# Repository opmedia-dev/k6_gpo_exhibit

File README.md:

# K6 GPO Exhibit

ESP32-based interface that lets an **unmodified** GPO 232 or 332 rotary-dial
telephone work as an interactive exhibit in a K6 phone box.

## Features

- **Random ringing** — the phone rings at configurable random intervals
  (default 5-30 min); answering plays a randomly selected history track
- **Dial-a-number** — dial up to 11 digits; if a matching MP3 exists on the
  SD card it plays, otherwise a "number not recognised" message plays
- **External control box** — three buttons (RING / CANCEL / RESET) on the
  operator's equipment box, connected via an extended lead
- **Full GPO phone interface** — hook detection, rotary pulse decoding, bell
  ringing (25 Hz UK cadence), all through the original 3-core cord
- **SD card audio** — all audio (history tracks, number tracks, dial tone,
  busy tone) loaded from a micro-SD card as MP3 files
- **I2S audio output** — MAX98357A DAC for quality playback through the
  phone's earpiece via a coupling transformer
- **Optional A+B coin box** — auto-detected daughter board supports classic
  GPO pre-payment coin mechanisms (Button A/B, coin weight switch)
- **Auto/Manual mode** — 4th button toggles auto-ring on/off with panel lamp
  indicator (GPIO 13, 3–6 V)
- **Wi-Fi file manager** — ESP32 creates a `K6-Exhibit` Wi-Fi hotspot;
  connect from any phone/laptop browser to upload, delete, and manage
  SD card files without removing the card
- **OTA firmware update** — upload a compiled `.bin` through the web
  interface to update firmware wirelessly
- **System & call logging** — separate logs for system events and call
  history, viewable and clearable via the web interface

No modifications are made to the telephone.

## Supported Phones

| Phone | Bell | Notes |
|-------|------|-------|
| GPO 232 | External (Bellset No. 26) | Blue wire drives external bell, or leave unconnected |
| GPO 332 | Internal (2 µF cap + bell coils) | Full bell ringing via blue wire |
| GPO 332L | Internal | "Listener" variant, same 3-wire connection |

Any GPO phone with a 3-wire connection (Line A, Line B, Bell) should work.
See the hardware docs for notes on other models (706, 746, etc.).

## System Architecture

```
┌─────────────┐   3-core cord    ┌─────────────────────────────┐
│  GPO Phone  │ ◄──────────────► │   ESP32 Interface Board     │
│  (unmod.)   │  extended lead   │   (in separate enclosure)   │
└─────────────┘                  │                             │
                                 │  ESP32 DevKit               │
                                 │  + SD card module           │
                                 │  + MAX98357A I2S DAC        │
                                 │  + L293D H-bridge (ringer)  │
                                 │  + 12V adapter → buck (5V)  │
                                 │  + 48V adapter (bell supply)│
                                 │  + Optocoupler (line sense) │
                                 │  + 4 control buttons        │
                                 └─────────────────────────────┘
```

## Hardware

See [`docs/hardware/`](docs/hardware/) for:
- [**Schematic**](docs/hardware/schematic.md) — full circuit with ASCII diagrams
- [**Bill of Materials**](docs/hardware/bom.md) — ~£29 in components
- [**Wiring Guide**](docs/hardware/wiring-guide.md) — step-by-step build + test

### PCB

A KiCad carrier board layout is in [`pcb/`](pcb/) — 100 × 100 mm, 2-layer,
all through-hole.  All modules (ESP32 DevKit, MAX98357A, SD card, LM2596
buck converter) plug in via pin headers; the bell runs from a dedicated
48 V adapter.  The **as-built, bench-proven manufacturing master is
[`pcb/k6_carrier_rev2-8.kicad_pcb`](pcb/k6_carrier_rev2-8.kicad_pcb)** —
use it for reorders.  See [`pcb/README.md`](pcb/README.md) for fabrication
instructions.

## SD Card Setup

Format a micro-SD card as FAT32 and create this directory structure:

```
/system/
    dialtone.mp3           Continuous dial tone (loops while off-hook)
    busy.mp3               Busy / error tone (loops)
    not_recognised.mp3     "The number you have dialled…"
/history/
    001.mp3                History track 1 (picked at random on ring answer)
    002.mp3                History track 2
    …
/numbers/
    999.mp3                Plays when user dials 999
    100.mp3                Plays when user dials 100
    08001111.mp3           Plays when user dials 08001111
    …
```

- History tracks play when the phone rings and is answered
- Number tracks are matched by filename: dialling `999` looks for `/numbers/999.mp3`
- If no match is found, `/system/not_recognised.mp3` plays

## Wi-Fi File Manager

The ESP32 creates a Wi-Fi access point on boot:

| Setting | Value |
|---------|-------|
| SSID | `K6-Exhibit` |
| Password | `phonebox` |
| URL | `http://192.168.4.1/` |

Connect with any phone or laptop, open a browser, and you can:
- **Controls** — volume slider, auto-ring timing, mode toggle, Ring Now button
- **Visitor stats** — call counters, most-dialled numbers, total uptime
- **Browse** the SD card directory structure
- **Upload** new MP3 files (validated as valid MP3 before saving)
- **Delete** existing files
- **Create** new folders
- **View logs** — system events and call history (separate tabs)
- **Clear logs** — wipe system or call log
- **Flash firmware** — upload a `.bin` file for OTA update
- **System status** — free heap, SD card space (used/total), current state

### Logs

| Log | Path | Contents |
|-----|------|----------|
| System | `/logs/system.log` | Boot, Wi-Fi, SD card, mode changes, OTA, errors |
| Calls | `/logs/calls.log` | Incoming/outgoing calls with timestamps, numbers, outcomes |

Logs auto-rotate at 64 KB to avoid filling the SD card.

## Firmware

Built with [PlatformIO](https://platformio.org/) (Arduino framework for ESP32).

### Build & Flash

```bash
cd firmware
pio run                    # compile
pio run -t upload          # flash to ESP32
pio device monitor         # serial console (115200 baud)
```

### Serial Commands

| Command | Action |
|---------|--------|
| `R` | Ring the bell |
| `H` | Hang up / stop everything |
| `C` | Cancel ring / stop playback |
| `S` | Print current state + diagnostics |
| `A` | Toggle auto-ring on/off |
| `V0`-`V9` | Set volume (0 = min, 9 = max) |

### Control Panel Buttons

| Button | Function |
|--------|----------|
| RING (GPIO 32) | Manually trigger the phone bell |
| CANCEL (GPIO 33) | Cancel ringing / stop current playback |
| RESET (GPIO 27) | Full system restart |
| MODE (GPIO 14) | Toggle auto/manual ring mode |

All buttons are active-low (connect to GND when pressed); the ESP32's
internal pull-ups are enabled.

### Auto-Mode Indicator Lamp

GPIO 13 drives a 3–6 V panel lamp (active-high) that illuminates when
auto-ring mode is active.  In **auto mode** the phone rings at random
intervals (5–30 min) and the lamp is ON.  In **manual mode** the phone
only rings when the RING button is pressed and the lamp is OFF.
Calling (lifting the handset, dialling) works in both modes.

### Firmware Architecture

```
main.cpp                    Arduino setup/loop, serial commands
  └─ PhoneController        Top-level state machine
       ├─ PhoneLine         Hook detection via optocoupler + ADC
       ├─ RotaryDecoder     Dial pulse counting → digit
       ├─ BellDriver        25 Hz H-bridge with UK ring cadence
       ├─ AudioPlayer       SD card MP3 playback via I2S
       ├─ ControlPanel      3-button debounced input
       └─ CoinBox           Optional A+B coin box (auto-detected)
```

State machine:

```
             auto-ring timer
                  or
IDLE ──── BTN_RING/serial 'R' ──── RINGING ──── (answer) ──── PLAYING_HISTORY
  │                                                                 │
  │                                                            (on-hook)
  │                                                                 │
  └── (lift handset) ── DIAL_TONE ── DIALING ─┬── PLAYING_NUMBER ──┘
                                               │         │
                                               │    (playback ends) ── BUSY ── (on-hook) ── IDLE
                                               │
                              [A+B, recognised] ├── AWAIT_COINS ── (coins in) ── AWAIT_BTN_A
                                               │                   "press A" prompt
                              [A+B, coins in]  ├── AWAIT_BTN_A ── (Btn A) ── PLAYING_NUMBER
                                               │                  (Btn B) ── IDLE (refund)
                                               │
                          [A+B, not recognised] └── AWAIT_BTN_B ── (Btn B) ── IDLE (refund)
                                                    "not recognised" then "press B" prompt

Without A+B: DIALING → PLAYING_NUMBER or PLAYING_NOT_REC directly.
Incoming calls (RINGING → answer) never require A+B interaction.
```

### Callbacks

```cpp
phone.onDigit(       { /* each digit as dialled */ });
phone.onNumber(  { /* complete number string */ });
phone.onHook(      { /* hook state change */     });
phone.onState(    { /* state transition */      });
```

## Pin Assignments

| GPIO | Function |
|------|----------|
| 34 | Line sense (hook / dial pulse) — ADC input |
| 26 | I2S BCLK (to MAX98357A) |
| 25 | I2S LRCLK (to MAX98357A) |
| 22 | I2S DOUT (to MAX98357A) |
| 5 | SD card CS (SPI) |
| 23 | SD card MOSI |
| 19 | SD card MISO |
| 18 | SD card SCK |
| 4 | Ring enable (H-bridge EN) |
| 16 | Ring phase A (H-bridge IN1) |
| 17 | Ring phase B (H-bridge IN2) |
| 32 | Button: RING (active-low) |
| 33 | Button: CANCEL (active-low) |
| 27 | Button: RESET (active-low) |
| 14 | Button: MODE (active-low) |
| 13 | Auto-mode lamp (active-high, 3–6 V) |
| 2 | Status LED |
| 36 | Coin box: coin sense (optional, input-only) |
| 39 | Coin box: Button A (optional, input-only) |
| 35 | Coin box: Button B (optional, input-only) |

## Technical Reference

See [`docs/gpo-phone-reference.md`](docs/gpo-phone-reference.md) for detailed
GPO 232/332 electrical specifications, rotary dial pulse characteristics, and
bell ringing requirements.

## Future Enhancements

- **Wi-Fi / MQTT** integration for remote exhibit control
- **Multi-phone networking** — connect two GPO phones via ESP-NOW
- **VoIP gateway** — bridge the GPO phone to SIP/VoIP
- **A+B coin box daughter board** — PCB design for coin mechanism interface
- **OLED status display** on the operator's control box

## License

MIT

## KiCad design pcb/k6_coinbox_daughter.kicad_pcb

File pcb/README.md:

# PCB — K6 GPO Exhibit Carrier Board

KiCad 10 project for a 2-layer carrier board (100 × 100 mm).  All modules
plug in via through-hole pin headers — no SMD soldering required.

See **[PINOUT.md](PINOUT.md)** for the complete pinout reference with every
pin, net, and signal described.

## Files

| File | Description |
|------|-------------|
| `k6_gpo_carrier.kicad_pro` | KiCad project file |
| `k6_gpo_carrier.kicad_sch` | Schematic (text-documentation style — shows all nets and pin assignments) |
| `k6_gpo_carrier.kicad_pcb` | PCB layout with component placement, ground-fill zones, and board outline |
| `generate_kicad.py` | Python script that generates all files above (run to regenerate) |
| `PINOUT.md` | Complete pinout reference (full tables for every connector and IC) |
| `k6_carrier_rev2-8.kicad_pcb` | **Hand-routed manufacturing master (Rev 2.1, as-built & bench-proven).** Use this file for reorders. Includes the Rev 2.1 fixes: R7 (R_LIM 2.2 kΩ) and D1 in series in the opto leg, C3 (10 µF/63 V coupling cap) in series with the transformer secondary, and R2 (470 Ω) as the opto-LED shunt. Power/48 V nets widened. Not generated by the scripts — edit here directly. |

> **Reorders:** fabricate from `k6_carrier_rev2-8.kicad_pcb`. The
> `generate_*.py` scripts produce the earlier auto-layout boards and do
> **not** include the hand-routed Rev 2.1 corrections above — regenerating
> will not reproduce this master. Before ordering: continuity-check the
> built board, confirm R7 is populated in series, and confirm D1's banded
> (cathode) end faces the PC817 side.

## Board Specifications

| Parameter | Value |
|-----------|-------|
| Dimensions | 100 × 100 mm |
| Layers | 2 (F.Cu + B.Cu) |
| Copper weight | 1 oz |
| Board thickness | 1.6 mm |
| Mounting holes | 4× M3, 4 mm from edges |
| Min trace width | 0.5 mm (power) / 0.25 mm (signal) |
| Min drill | 0.4 mm (vias), 0.8 mm (IC pads), 1.0 mm (headers) |

## Component Placement

```
┌──────────────────────────────────────────────────────────────────────────────┐
│ (MH)  [12V IN]  [BUCK]   [BOOST]                [MAX98357A] [DAC] (MH)     │
│         J3       J1        J2                      J5        J6             │
│                                                                             │
│                                                    [XFMR T1]               │
│                 ┌─────────────────────┐                                     │
│                 │                     │            [PHONE J4]               │
│                 │    ESP32 DevKit     │             3-pin screw             │
│                 │        U1           │                                     │
│ [BUTTONS]       │  2×15 pin headers   │                                     │
│  J8 RING        └─────────────────────┘       [C1]                         │
│  J9 CANCEL                                                                  │
│  J10 RESET                                    ┌────────┐                   │
│                                               │ L293D  │                   │
│                                               │  U2    │                   │
│                 [R1 470R]  [R2 220R]          └────────┘  [R3 10K]         │
│ [SD CARD]                                     ┌────┐                       │
│  J7                                           │PC817│                      │
│                                               │ U3  │                      │
│ (MH)                                          └────┘            (MH)       │
└──────────────────────────────────────────────────────────────────────────────┘
  (MH) = Mounting hole M3
```

## Connectors

| Ref | Description | Pins |
|-----|-------------|------|
| J1 | LM2596 buck converter (12V → 5V) | 4: IN+, IN-, OUT+, OUT- |
| J2 | XL6009 boost converter (12V → 50V) | 4: IN+, IN-, OUT+, OUT- |
| J3 | 12V DC power input | 2: +12V, GND |
| J4 | Phone cord (3-pin screw terminal) | 3: Line A, Line B, Bell |
| J5 | MAX98357A DAC module | 7: VIN, GND, SD, GAIN, DIN, BCLK, LRC |
| J6 | DAC audio output (to transformer) | 2: L+, L- |
| J7 | SD card module (SPI) | 6: GND, VCC, MOSI, MISO, SCK, CS |
| J8 | RING button (to control panel) | 2: signal, GND |
| J9 | CANCEL button (to control panel) | 2: signal, GND |
| J10 | RESET button (to control panel) | 2: signal, GND |

## ICs

| Ref | Part | Package |
|-----|------|---------|
| U1 | ESP32 DevKit V1 | 2×15 pin header socket (25.4 mm row spacing) |
| U2 | L293D H-bridge | DIP-16 (use IC socket) |
| U3 | PC817 optocoupler | DIP-4 (use IC socket) |

## Passive Components

| Ref | Value | Purpose |
|-----|-------|---------|
| R1 | 470 Ω 1W | Line current limit |
| R2 | 220 Ω ¼W | Optocoupler LED current limit |
| R3 | 10 kΩ ¼W | Optocoupler output pull-down |
| C1 | 100 nF | L293D decoupling capacitor |
| T1 | 600 Ω : 600 Ω transformer | Audio coupling to phone line |

## Fabrication

### Ordering from JLCPCB / PCBWay

1. Open the project in KiCad 10+
2. **File → Plot** → select Gerber format, output to `gerbers/`
3. Check layers: F.Cu, B.Cu, F.SilkS, B.SilkS, F.Mask, B.Mask, Edge.Cuts
4. **Generate Drill Files** → Excellon format
5. Zip the `gerbers/` folder and upload to your fabricator

Typical 5-board order from JLCPCB: ~$2 + shipping.

### Assembly Notes

1. Solder IC sockets first (U2 DIP-16, U3 DIP-4)
2. Solder resistors and capacitor
3. Solder pin headers for all module connectors
4. Solder screw terminals (J3 power, J4 phone)
5. Solder transformer T1
6. Insert ICs into sockets (mind pin 1 orientation)
7. Plug in modules: ESP32, MAX98357A, SD card, buck converter, boost converter

## Regenerating Files

If you modify the board layout, edit `generate_kicad.py` and run:

```bash
cd pcb
python3 generate_kicad.py
```

This regenerates all three KiCad files from scratch.

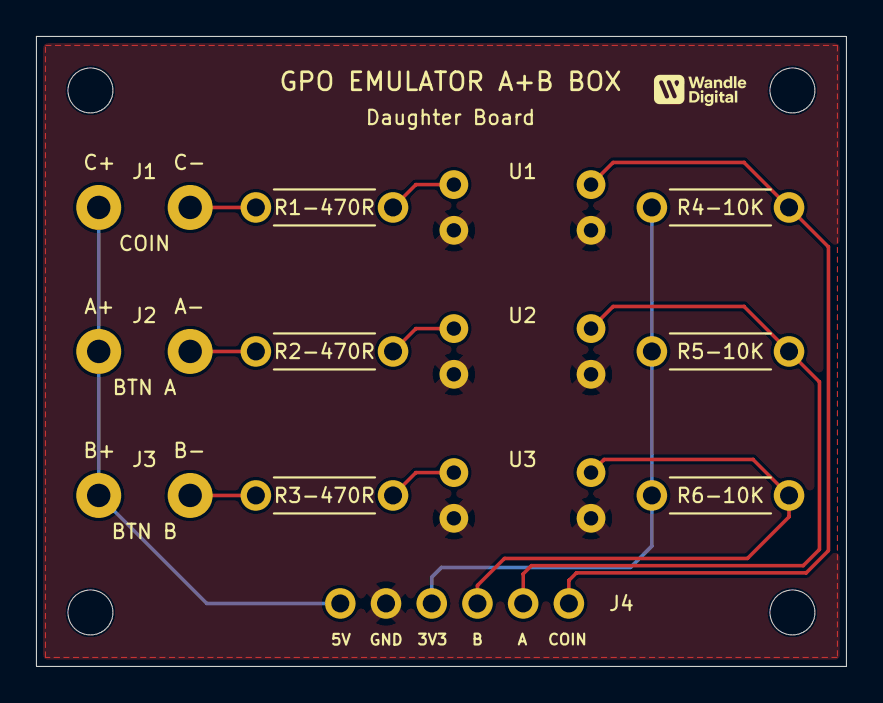
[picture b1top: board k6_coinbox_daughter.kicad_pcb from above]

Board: 2 copper layers, 45.0 x 35.0 mm, 17 parts (0 on the bottom side), 12 nets.

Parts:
J1: COIN; J1
J2: BTN_A; J2
J3: BTN_B; J3
J4: TO_ESP32; J4
MH1: MH; MH1
MH2: MH; MH2
MH3: MH; MH3
MH4: MH; MH4
R1-470R: 470R; R1
R2-470R: 470R; R2
R3-470R: 470R; R3
R4-10K: 10K; R4
R5-10K: 10K; R5
R6-10K: 10K; R6
U1: PC817; U1
U2: PC817; U2
U3: PC817; U3

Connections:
BTNA_IN_B: J2.2, R2-470R.1
BTNB_IN_B: J3.2, R3-470R.1
BTN_A: J4.2, R5-10K.2, U2.4
BTN_B: J4.3, R6-10K.2, U3.4
COIN_IN_B: J1.2, R1-470R.1
COIN_SENSE: J4.1, R4-10K.2, U1.4
GND: J4.5, U1.2, U1.3, U2.2, U2.3, U3.2, U3.3
OPTO1_CA: R1-470R.2, U1.1
OPTO2_CA: R2-470R.2, U2.1
OPTO3_CA: R3-470R.2, U3.1
VCC_3V3: J4.4, R4-10K.1, R5-10K.1, R6-10K.1
VCC_5V: J1.1, J2.1, J3.1, J4.6

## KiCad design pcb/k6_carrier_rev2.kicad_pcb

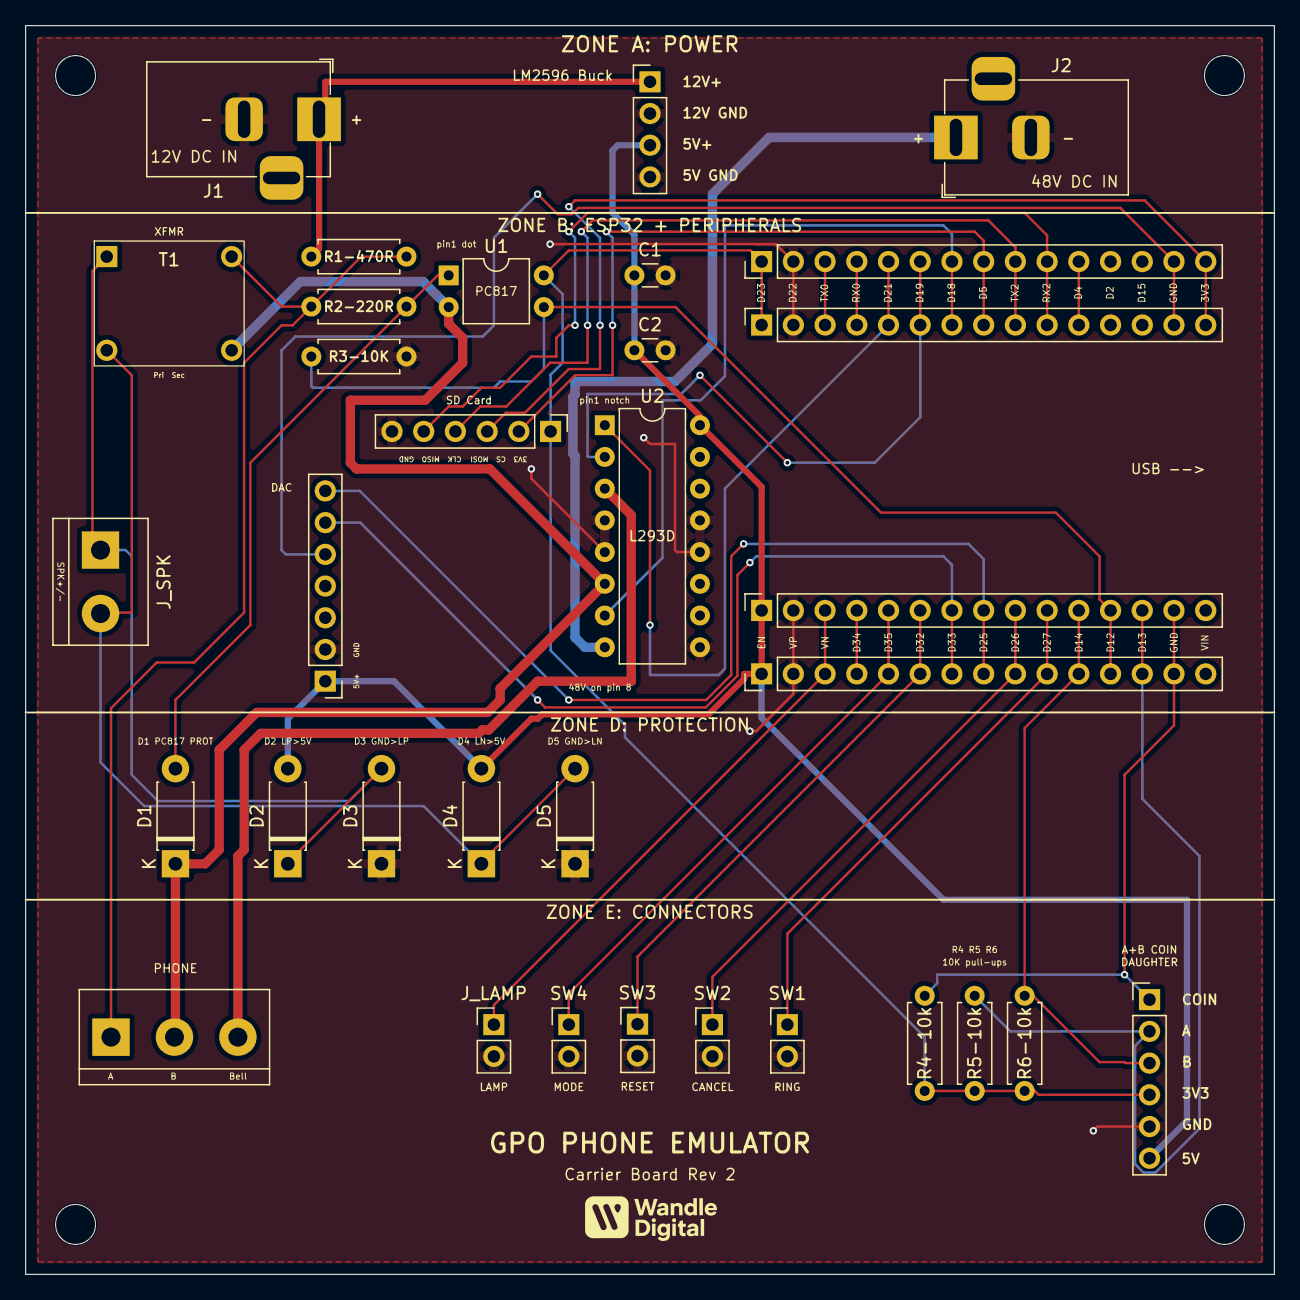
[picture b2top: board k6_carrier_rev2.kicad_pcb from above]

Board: 2 copper layers, 100.0 x 100.0 mm, 37 parts (0 on the bottom side), 34 nets.

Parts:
C1, C2: 100nF; C_Disc_D3.0mm_W1.6mm_P2.50mm
D1, D2, D3, D4, D5: 1N4007; D_DO-41_SOD81_P7.62mm_Horizontal
H1, H2, H3, H4: M3; MountingHole_3.2mm_M3
J1: 12V_DC; BarrelJack_Horizontal
J2: 48V_DC; BarrelJack_Horizontal
J_COIN: A+B; PinHeader_1x06_P2.54mm_Vertical
J_DEV_L: DEV_Left; PinHeader_1x15_P2.54mm_Vertical
J_DEV_R: DEV_Right; PinHeader_1x15_P2.54mm_Vertical
J_ESP_L: ESP32_Left; PinSocket_1x15_P2.54mm_Vertical
J_ESP_R: ESP32_Right; PinSocket_1x15_P2.54mm_Vertical
J_LAMP: Lamp; PinHeader_1x02_P2.54mm_Vertical
J_PHONE: Phone; TerminalBlock_bornier-3_P5.08mm
J_SPK: Speaker; TerminalBlock_bornier-2_P5.08mm
R1-470R: R2-470R; R_Axial_DIN0207_L6.3mm_D2.5mm_P7.62mm_Horizontal
R2-220R: R3-220R; R_Axial_DIN0207_L6.3mm_D2.5mm_P7.62mm_Horizontal
R3-10K, R4-10k, R5-10k, R6-10k: 10K; R_Axial_DIN0207_L6.3mm_D2.5mm_P7.62mm_Horizontal
SW1: RING; PinHeader_1x02_P2.54mm_Vertical
SW2: CANCEL; PinHeader_1x02_P2.54mm_Vertical
SW3: RESET; PinHeader_1x02_P2.54mm_Vertical
SW4: MODE; PinHeader_1x02_P2.54mm_Vertical
T1: 600R_XFMR; PinHeader_2x02_P2.54mm_Vertical
U1: PC817; DIP-4_W7.62mm
U2: L293D; DIP-16_W7.62mm
U_BUCK: LM2596; PinHeader_1x04_P2.54mm_Vertical
U_DAC: MAX98357A; PinHeader_1x07_P2.54mm_Vertical
U_SD: SD_Card; PinHeader_1x06_P2.54mm_Vertical

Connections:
+3V3: J_COIN.4, J_DEV_R.1, J_ESP_R.1, R4-10k.1, R5-10k.1, R6-10k.1, U1.4, U_SD.1
+5V: C1.1, C2.1, D2.2, D4.2, J_COIN.6, J_DEV_L.1, J_ESP_L.1, U2.16, U_BUCK.3, U_DAC.1
+12V: J1.1, R1-470R.1, U_BUCK.1
+48V: J2.1, U2.8
BELL: J_PHONE.3, U2.3
DAC_LN: D4.1, D5.2, J_SPK.2, T1.3
DAC_LP: D2.1, D3.2, J_SPK.1, T1.1
GND: C1.2, C2.2, D3.1, D5.1, J1.2, J2.2, J_COIN.5, J_DEV_L.2, J_DEV_R.2, J_ESP_L.2, J_ESP_R.2, J_LAMP.2, R3-10K.2, SW1.2, SW2.2, SW3.2, SW4.2, U2.4, U2.5, U2.9, U2.12, U2.13, U_BUCK.2, U_BUCK.4, U_DAC.2, U_SD.6
GPIO2: J_DEV_R.4, J_ESP_R.4
GPIO4: J_DEV_R.5, J_ESP_R.5, U2.1
GPIO5: J_DEV_R.8, J_ESP_R.8, U_SD.2
GPIO12: J_DEV_L.4, J_ESP_L.4
GPIO13: J_DEV_L.3, J_ESP_L.3, J_LAMP.1
GPIO14: J_DEV_L.5, J_ESP_L.5, SW4.1
GPIO15: J_DEV_R.3, J_ESP_R.3
GPIO16: J_DEV_R.6, J_ESP_R.6, U2.2
GPIO17: J_DEV_R.7, J_ESP_R.7, U2.7
GPIO18: J_DEV_R.9, J_ESP_R.9, U_SD.4
GPIO19: J_DEV_R.10, J_ESP_R.10, U_SD.5
GPIO21: J_DEV_R.11, J_ESP_R.11
GPIO22: J_DEV_R.14, J_ESP_R.14, U_DAC.5
GPIO23: J_DEV_R.15, J_ESP_R.15, U_SD.3
GPIO25: J_DEV_L.8, J_ESP_L.8, U_DAC.7
GPIO26: J_DEV_L.7, J_ESP_L.7, U_DAC.6
GPIO27: J_DEV_L.6, J_ESP_L.6, SW3.1
GPIO32: J_DEV_L.10, J_ESP_L.10, SW1.1
GPIO33: J_DEV_L.9, J_ESP_L.9, SW2.1
GPIO34: J_DEV_L.12, J_ESP_L.12, R3-10K.1, U1.3
GPIO35: J_COIN.3, J_DEV_L.11, J_ESP_L.11, R6-10k.2
GPIO36: J_COIN.1, J_DEV_L.14, J_ESP_L.14, R4-10k.2
GPIO39: J_COIN.2, J_DEV_L.13, J_ESP_L.13, R5-10k.2
LINE_A: J_PHONE.1, R1-470R.2, R2-220R.1, T1.2
LINE_B: D1.1, J_PHONE.2, T1.4, U1.2, U2.6
OPTO_A: D1.2, R2-220R.2, U1.1

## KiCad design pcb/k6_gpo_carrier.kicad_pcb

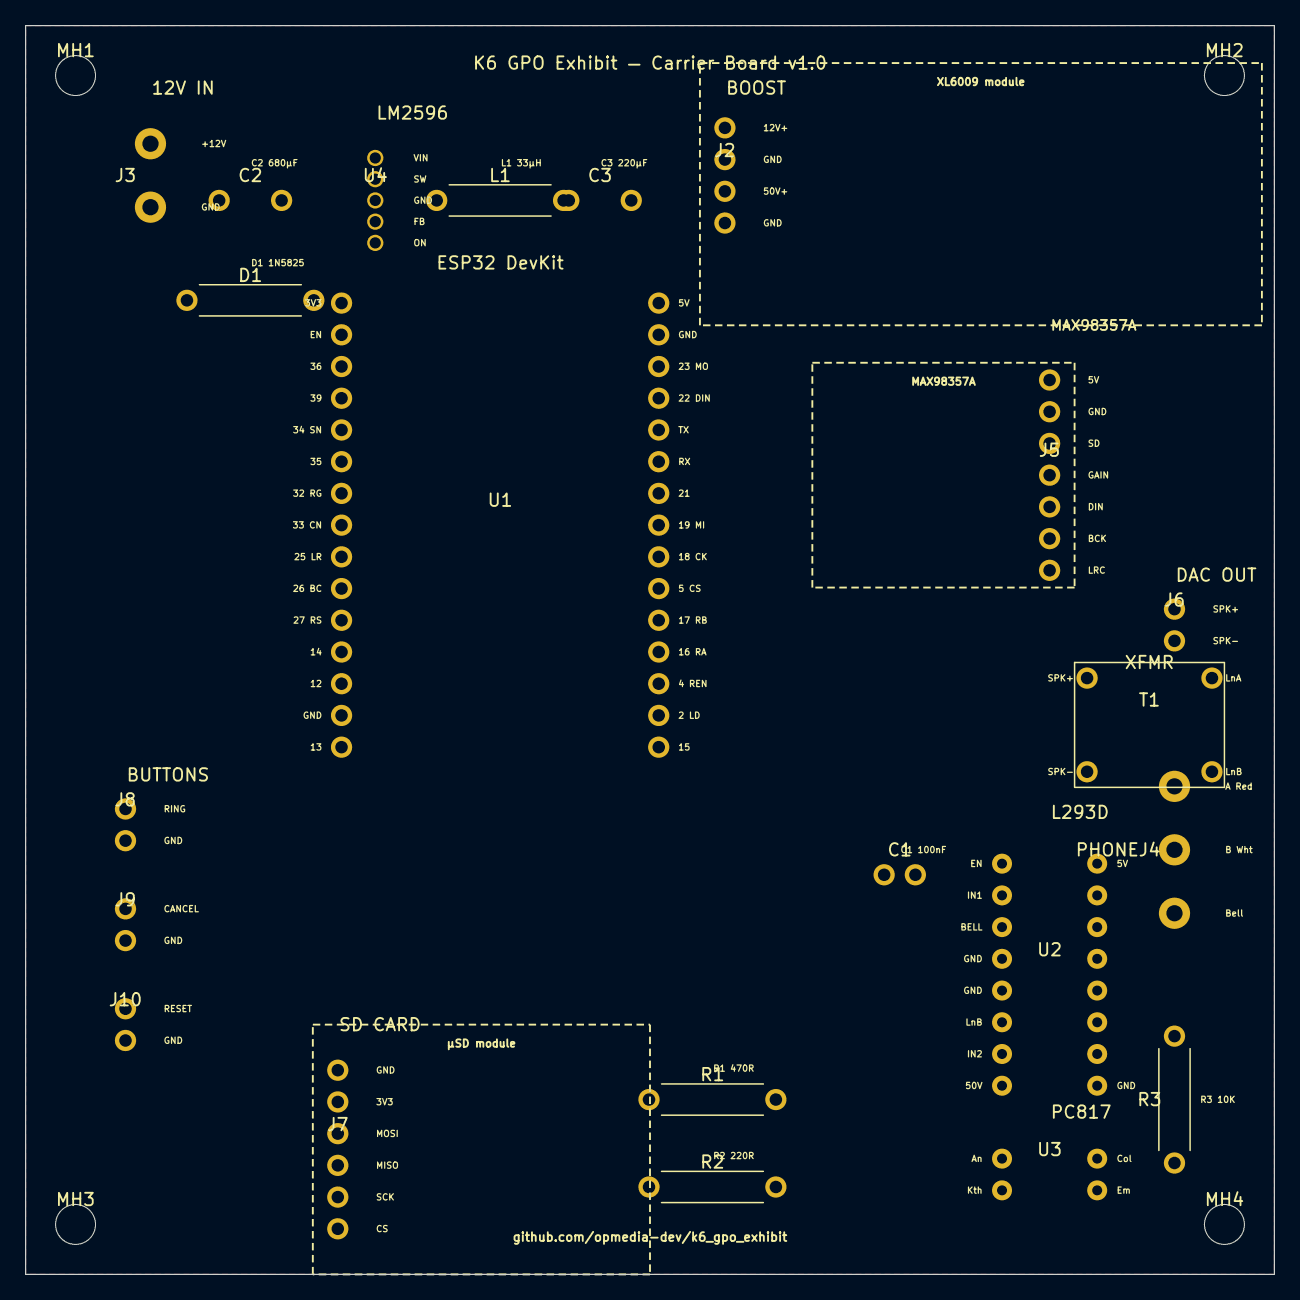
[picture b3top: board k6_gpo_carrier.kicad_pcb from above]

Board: 2 copper layers, 100.0 x 100.0 mm, 26 parts (0 on the bottom side), 27 nets, no tracks yet.

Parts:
C1: 100nF; C1
C2: 680uF; C2
C3: 220uF; C3
D1: 1N5825; D1
J2: XL6009_Boost; J2
J3: 12V_IN; J3
J4: PHONE; J4
J5: MAX98357A; J5
J6: DAC_OUT; J6
J7: SD_Card; J7
J8: BTN_RING; J8
J9: BTN_CANCEL; J9
J10: BTN_RESET; J10
L1: 33uH; L1
MH1: MH; MH1
MH2: MH; MH2
MH3: MH; MH3
MH4: MH; MH4
R1: 470R; R1
R2: 220R; R2
R3: 10K; R3
T1: 600R_XFMR; T1
U1: ESP32_DevKit; U1
U2: L293D; U2
U3: PC817; U3
U4: LM2596-5.0; U4

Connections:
+3V3: J7.2, U1.L1, U3.4
+5V: C1.1, C3.1, J5.1, L1.2, U1.R1, U2.16, U4.4
+12V: C2.1, J2.1, J3.1, R1.1, U4.1
+50V: J2.3, U2.8
AUDIO_P1: J6.1, T1.1
AUDIO_P2: J6.2, T1.2
BELL: J4.3, U2.3
BTN_CANCEL: J9.1, U1.L8
BTN_RESET: J10.1, U1.L11
BTN_RING: J8.1, U1.L7
GND: C1.2, C2.2, C3.2, D1.1, J2.2, J2.4, J3.2, J5.2, J7.1, J8.2, J9.2, J10.2, R3.2, U1.L14, U1.R2, U2.4, U2.5, U2.9, U2.12, U2.13, U4.3, U4.5
I2S_BCLK: J5.6, U1.L10
I2S_DOUT: J5.5, U1.R4
I2S_LRCLK: J5.7, U1.L9
JUNC_A: R1.2, R2.1
LINE_A: J4.1, T1.3
LINE_B: J4.2, T1.4, U2.6, U3.2
OPTO_ANODE: R2.2, U3.1
OPTO_EMIT: R3.1, U3.3
RING_A: U1.R12, U2.2
RING_B: U1.R11, U2.7
RING_EN: U1.R13, U2.1
SD_CS: J7.6, U1.R10
SPI_MISO: J7.4, U1.R8
SPI_MOSI: J7.3, U1.R3
SPI_SCK: J7.5, U1.R9
SW_OUT: D1.2, L1.1, U4.2

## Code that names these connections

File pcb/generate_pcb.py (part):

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
    # ── Nets ──
    net_names = ["", "GND", "+5V", "+3V3", "+12V", "+48V",
        "GPIO4", "GPIO16", "GPIO17", "GPIO26", "GPIO25", "GPIO22",
        "GPIO5", "GPIO23", "GPIO19", "GPIO18",
        "GPIO32", "GPIO33", "GPIO27", "GPIO14",
        "GPIO36", "GPIO39", "GPIO35", "GPIO13", "GPIO34", "GPIO2",
        "LINE_A", "LINE_B", "BELL", "OPTO_A", "DAC_LP", "DAC_LN",
        "GPIO12", "GPIO15", "GPIO21"]
    for i, n in enumerate(net_names):
        board.Add(pcbnew.NETINFO_ITEM(board, n, i))

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    # ── ZONE D: PROTECTION DIODES (y = 57..70mm) ──

    # D1: 1N4007 anti-parallel across PC817 LED (clamps reverse voltage)
    # Anode = LINE_B (PC817 cathode side), Cathode = OPTO_A (PC817 anode side)
    place(board, "Diode_THT", "D_DO-41_SOD81_P7.62mm_Horizontal",
          "D1", "1N4007", OX+10, OY+60)
    text(board, "D1 PC817 PROT", OX+14, OY+57, S, 0.5, 0.08)
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    esp_l_nets = {
        1: "+5V",      # VIN
        2: "GND",
        3: "GPIO13",
        4: "GPIO12",
        5: "GPIO14",
        6: "GPIO27",
        7: "GPIO26",
        8: "GPIO25",
        9: "GPIO33",
        10: "GPIO32",
        11: "GPIO35",
        12: "GPIO34",
        13: "GPIO39",   # VN
        14: "GPIO36",   # VP
        # 15: EN — no net
    }
    for p, n in esp_l_nets.items():
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    esp_r_nets = {
        1: "+3V3",
        2: "GND",
        3: "GPIO15",
        4: "GPIO2",
        5: "GPIO4",
        6: "GPIO16",   # RX2
        7: "GPIO17",   # TX2
        8: "GPIO5",
        9: "GPIO18",
        10: "GPIO19",
        11: "GPIO21",
        # 12: RX0 — no net (serial debug)
        # 13: TX0 — no net (serial debug)
        14: "GPIO22",
        15: "GPIO23",
    }
    for p, n in esp_r_nets.items():
        set_pad_net("J_ESP_R", p, n)
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
    # ── U1 (PC817 optocoupler DIP-4) ──
    # Pin 1=Anode (from R2), Pin 2=Cathode (to Line B),
    # Pin 3=Emitter (GPIO34+R3), Pin 4=Collector (+3.3V)
    set_pad_net("U1", 1, "OPTO_A")
    set_pad_net("U1", 2, "LINE_B")
    set_pad_net("U1", 3, "GPIO34")
    set_pad_net("U1", 4, "+3V3")

    # ── R1 (470Ω) ──  pad 1 = +12V, pad 2 = LINE_A
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    set_pad_net("R2", 1, "LINE_A")
    set_pad_net("R2", 2, "OPTO_A")

    # ── R3 (10kΩ) ──  pad 1 = GPIO34 (opto emitter), pad 2 = GND
    set_pad_net("R3", 1, "GPIO34")
    set_pad_net("R3", 2, "GND")

    # ── U_DAC (MAX98357A 7-pin header) ──
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    set_pad_net("U_DAC", 2, "GND")
    # pin 3 (SD) — leave unconnected (floats high = always on)
    # pin 4 (GAIN) — leave unconnected (default 9dB)
    set_pad_net("U_DAC", 5, "GPIO22")  # DIN
    set_pad_net("U_DAC", 6, "GPIO26")  # BCLK
    set_pad_net("U_DAC", 7, "GPIO25")  # LRC

    # ── J_SPK (speaker screw terminal 2-pin) ──
    # Connects DAC speaker output to transformer primary
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
    # ── U_SD (SD card 6-pin header: 3V3 CS MOSI CLK MISO GND) ──
    set_pad_net("U_SD", 1, "+3V3")     # 3V3
    set_pad_net("U_SD", 2, "GPIO5")    # CS
    set_pad_net("U_SD", 3, "GPIO23")   # MOSI
    set_pad_net("U_SD", 4, "GPIO18")   # CLK
    set_pad_net("U_SD", 5, "GPIO19")   # MISO
    set_pad_net("U_SD", 6, "GND")

    # ── U2 (L293D H-bridge DIP-16) ──
    set_pad_net("U2", 1, "GPIO4")      # EN1,2
    set_pad_net("U2", 2, "GPIO16")     # IN1
    set_pad_net("U2", 3, "BELL")       # OUT1 → Terminal 3 (Bell)
    set_pad_net("U2", 4, "GND")
    set_pad_net("U2", 5, "GND")
    set_pad_net("U2", 6, "LINE_B")     # OUT2 → Terminal 2 (Line B)
    set_pad_net("U2", 7, "GPIO17")     # IN2
    set_pad_net("U2", 8, "+48V")       # VS (motor supply)
    set_pad_net("U2", 9, "GND")
    set_pad_net("U2", 12, "GND")
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    set_pad_net("J_PHONE", 3, "BELL")    # Terminal 3 (Blue / Bell)

    # ── SW1-4 (buttons: pin 1 = GPIO, pin 2 = GND) ──
    set_pad_net("SW1", 1, "GPIO32"); set_pad_net("SW1", 2, "GND")
    set_pad_net("SW2", 1, "GPIO33"); set_pad_net("SW2", 2, "GND")
    set_pad_net("SW3", 1, "GPIO27"); set_pad_net("SW3", 2, "GND")
    set_pad_net("SW4", 1, "GPIO14"); set_pad_net("SW4", 2, "GND")

    # ── J_LAMP (panel lamp 2-pin: GPIO13 + GND) ──
    set_pad_net("J_LAMP", 1, "GPIO13")
    set_pad_net("J_LAMP", 2, "GND")

    # ── R4/R5/R6 (10kΩ pull-ups: pad 1 = +3V3, pad 2 = GPIO) ──
    set_pad_net("R4", 1, "+3V3");  set_pad_net("R4", 2, "GPIO36")
    set_pad_net("R5", 1, "+3V3");  set_pad_net("R5", 2, "GPIO39")
    set_pad_net("R6", 1, "+3V3");  set_pad_net("R6", 2, "GPIO35")

    # ── J_COIN (daughter board 6-pin header) ──
    set_pad_net("J_COIN", 1, "GPIO36")   # COIN_SENSE
    set_pad_net("J_COIN", 2, "GPIO39")   # BTN_A
    set_pad_net("J_COIN", 3, "GPIO35")   # BTN_B
    set_pad_net("J_COIN", 4, "+3V3")     # Power
    set_pad_net("J_COIN", 5, "GND")
    set_pad_net("J_COIN", 6, "+5V")      # Optional 5V
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
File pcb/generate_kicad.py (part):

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    7: "LINE_B",
    8: "BELL",
    9: "LINE_SENSE",      # GPIO 34
    10: "RING_EN",        # GPIO 4
    11: "RING_A",         # GPIO 16
    12: "RING_B",         # GPIO 17
    13: "I2S_BCLK",       # GPIO 26
    14: "I2S_LRCLK",      # GPIO 25
    15: "I2S_DOUT",       # GPIO 22
    16: "SD_CS",          # GPIO 5
    17: "SPI_MOSI",       # GPIO 23
    18: "SPI_MISO",       # GPIO 19
    19: "SPI_SCK",        # GPIO 18
    20: "BTN_RING",       # GPIO 32
    21: "BTN_CANCEL",     # GPIO 33
    22: "BTN_RESET",      # GPIO 27
    23: "OPTO_ANODE",
    24: "OPTO_EMIT",
    25: "AUDIO_P1",       # transformer primary 1
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        4: 0,     # GPIO 39
        5: 9,     # GPIO 34 → LINE_SENSE
        6: 0,     # GPIO 35
        7: 20,    # GPIO 32 → BTN_RING
        8: 21,    # GPIO 33 → BTN_CANCEL
        9: 14,    # GPIO 25 → I2S_LRCLK
        10: 13,   # GPIO 26 → I2S_BCLK
        11: 22,   # GPIO 27 → BTN_RESET
        12: 0,    # GPIO 14
        13: 0,    # GPIO 12
        14: 4,    # GND
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    esp_right = {
        1: 2,     # VIN → +5V
        2: 4,     # GND
        3: 17,    # GPIO 23 → SPI_MOSI
        4: 15,    # GPIO 22 → I2S_DOUT
        5: 0,     # TX0
        6: 0,     # RX0
        7: 0,     # GPIO 21
        8: 18,    # GPIO 19 → SPI_MISO
        9: 19,    # GPIO 18 → SPI_SCK
        10: 16,   # GPIO 5 → SD_CS
        11: 12,   # GPIO 17 → RING_B
        12: 11,   # GPIO 16 → RING_A
        13: 10,   # GPIO 4 → RING_EN
        14: 28,   # GPIO 2 → LED_STATUS
        15: 0,    # GPIO 15
    }
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
  (text "=== PHONE LINE INTERFACE ===" (at 177.8 25.4 0)
    (effects (font (size 2.54 2.54) (bold yes))))
  (text "J4: Phone Terminal Block (3-pin screw)\\nPin 1: LINE_A (Red)   Pin 2: LINE_B (White)   Pin 3: BELL (Blue)" (at 177.8 33.02 0)
    (effects (font (size 1.27 1.27)) (justify left)))

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
  (text "=== SD CARD ===" (at 25.4 160.02 0)
    (effects (font (size 2.54 2.54) (bold yes))))
  (text "J7: SD Card Module (6-pin header):\\nPin 1: GND     Pin 4: MISO (GPIO19)\\nPin 2: VCC (3V3)  Pin 5: SCK (GPIO18)\\nPin 3: MOSI (GPIO23)  Pin 6: CS (GPIO5)" (at 25.4 172.72 0)
    (effects (font (size 1.27 1.27)) (justify left)))

  (text "=== CONTROL PANEL ===" (at 25.4 193.04 0)
    (effects (font (size 2.54 2.54) (bold yes))))
  (text "J8: RING Button     Pin 1: GPIO32   Pin 2: GND\\nJ9: CANCEL Button   Pin 1: GPIO33   Pin 2: GND\\nJ10: RESET Button   Pin 1: GPIO27   Pin 2: GND\\n(All active-low, ESP32 internal pull-ups enabled)" (at 25.4 203.2 0)
    (effects (font (size 1.27 1.27)) (justify left)))

  (text "=== NET LIST ===" (at 177.8 193.04 0)
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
